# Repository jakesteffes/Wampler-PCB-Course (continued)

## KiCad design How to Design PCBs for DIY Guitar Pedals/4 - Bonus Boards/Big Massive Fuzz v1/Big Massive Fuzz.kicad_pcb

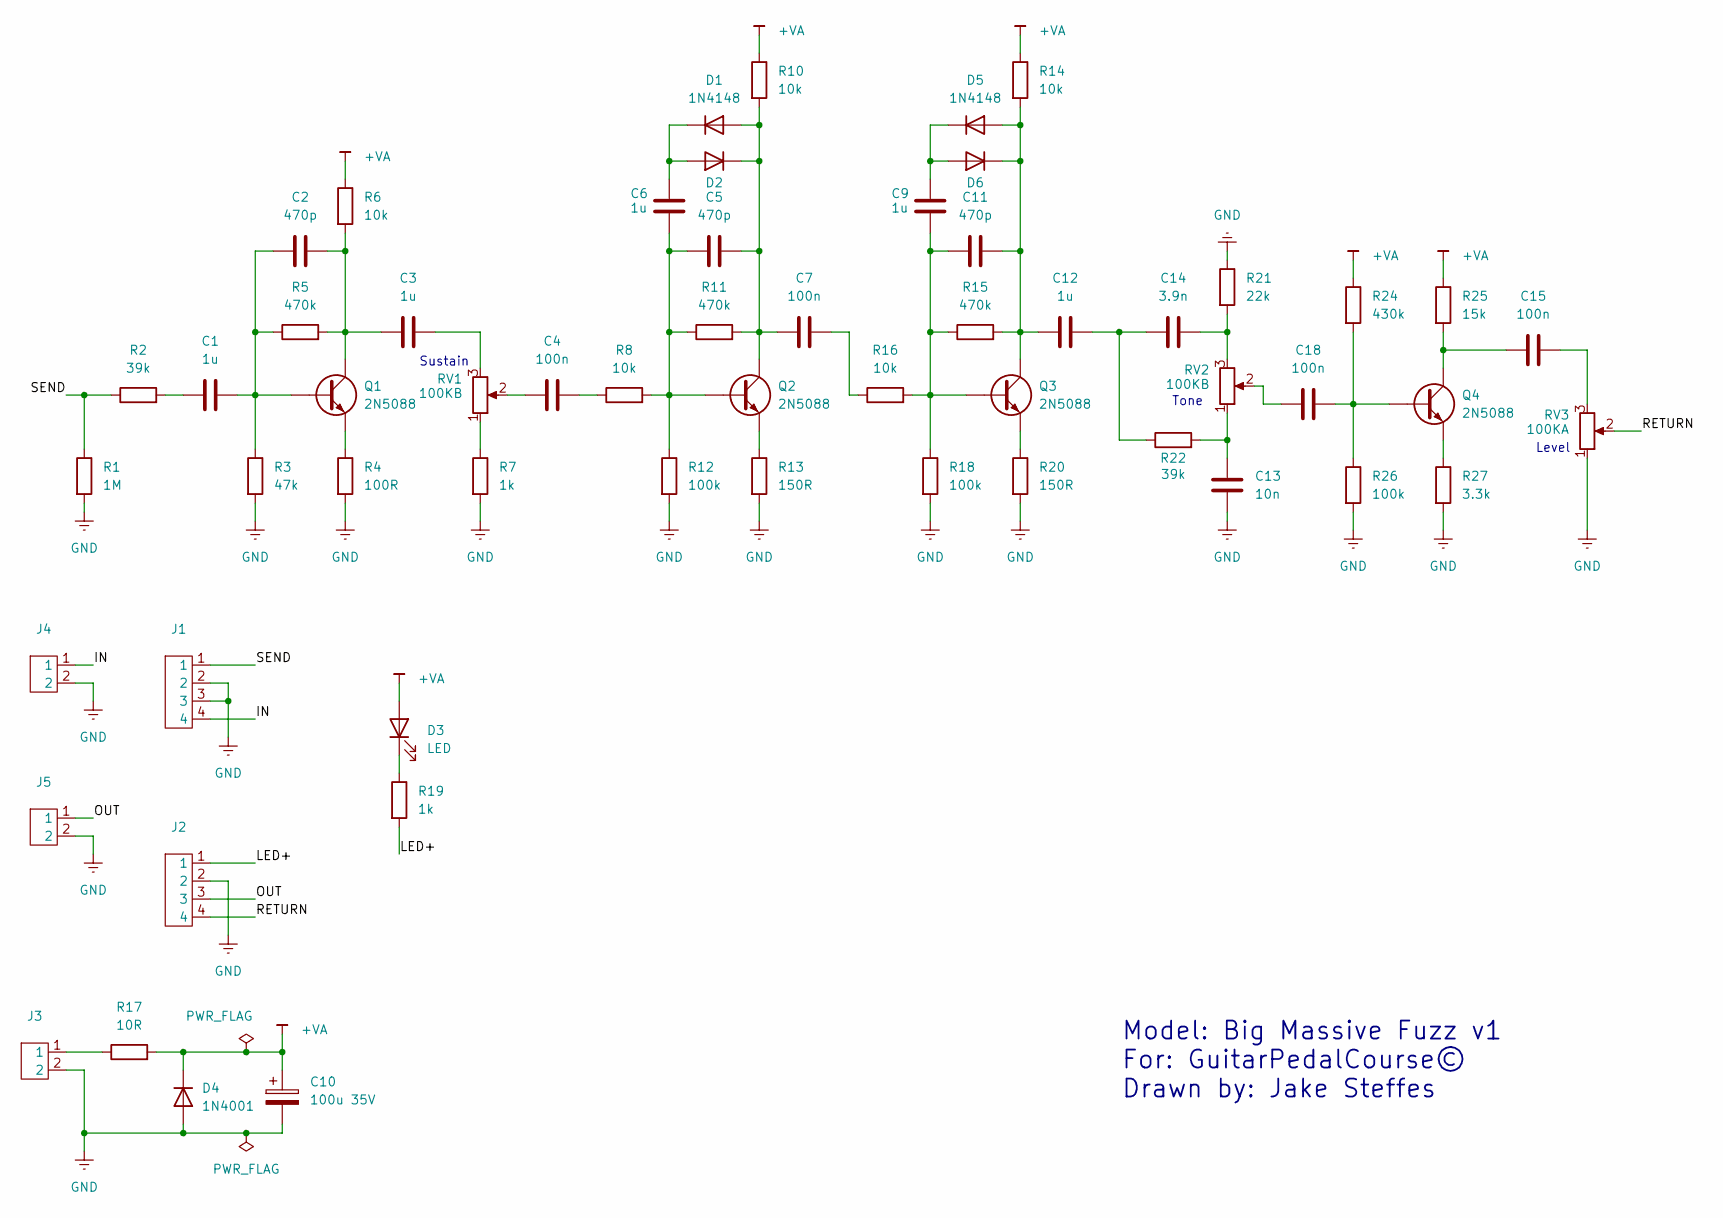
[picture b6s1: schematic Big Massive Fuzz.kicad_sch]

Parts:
C1, C3, C6, C9, C12: 1u; CAP_FILM_1UF
C2, C5, C11: 470p; CAP_MLCC_470PF
C4, C7, C15, C18: 100n; CAP_FILM_100NF
C10: 100u 35V; CAP_ELEC_100UF
C13: 10n; CAP_FILM_10NF
C14: 3.9n; CAP_MLCC_3.9NF
D1, D2, D5, D6: 1N4148; DIODE_1N4148
D3: LED; LED_5MM
D4: 1N4001; DIODE_1N4001
J1, J2: CONNECTOR_4
J3, J4, J5: CONNECTOR_2
Q1, Q2, Q3, Q4: 2N5088; BJT_2N5088
R1: 1M; RESISTOR_1_4W
R2, R22: 39k; RESISTOR_1_4W
R3: 47k; RESISTOR_1_4W
R4: 100R; RESISTOR_1_4W
R5, R11, R15: 470k; RESISTOR_1_4W
R6, R8, R10, R14, R16: 10k; RESISTOR_1_4W
R7, R19: 1k; RESISTOR_1_4W
R12, R18, R26: 100k; RESISTOR_1_4W
R13, R20: 150R; RESISTOR_1_4W
R17: 10R; RESISTOR_1_4W
R21: 22k; RESISTOR_1_4W
R24: 430k; RESISTOR_1_4W
R25: 15k; RESISTOR_1_4W
R27: 3.3k; RESISTOR_1_4W
RV1, RV2: 100KB; POT_16MM_RA
RV3: 100KA; POT_16MM_RA

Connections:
+VA: C10.1, D3.2 (A), D4.1 (K), R6.1, R10.1, R14.1, R17.2, R24.1, R25.1
/IN: J1.4, J4.1
/LED+: J2.1, R19.2
/OUT: J2.3, J5.1
/RETURN: J2.4, RV3.2
/SEND: J1.1, R1.1, R2.1
GND: C10.2, C13.1, D4.2 (A), J1.2, J1.3, J2.2, J3.2, J4.2, J5.2, R1.2, R3.2, R4.2, R7.2, R12.2, R13.2, R18.2, R20.2, R21.1, R26.2, R27.2, RV3.1
unnamed: C1.1, R2.2
unnamed: C1.2, C2.1, Q1.B, R3.1, R5.1
unnamed: C2.2, C3.1, Q1.C, R5.2, R6.2
unnamed: C3.2, RV1.3
unnamed: C4.1, RV1.2
unnamed: C4.2, R8.1
unnamed: C5.1, C6.1, Q2.B, R8.2, R11.1, R12.1
unnamed: C7.2, R16.1
unnamed: C9.1, C11.1, Q3.B, R15.1, R16.2, R18.1
unnamed: C12.2, C14.2, R22.1
unnamed: C13.2, R22.2, RV2.1
unnamed: C14.1, R21.2, RV2.3
unnamed: C15.1, Q4.C, R25.2
unnamed: C15.2, RV3.3
unnamed: C18.1, RV2.2
unnamed: C18.2, Q4.B, R24.2, R26.1
unnamed: C5.2, C7.1, D1.2 (A), D2.1 (K), Q2.C, R10.2, R11.2
unnamed: C6.2, D1.1 (K), D2.2 (A)
unnamed: D3.1 (K), R19.1
unnamed: C11.2, C12.1, D5.2 (A), D6.1 (K), Q3.C, R14.2, R15.2
unnamed: C9.2, D5.1 (K), D6.2 (A)
unnamed: J3.1, R17.1
unnamed: Q1.E, R4.1
unnamed: Q2.E, R13.1
unnamed: Q3.E, R20.1
unnamed: Q4.E, R27.1
unnamed: R7.1, RV1.1

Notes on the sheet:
Model: Big Massive Fuzz v1 For: GuitarPedalCourse© Drawn by: Jake Steffes
Level
Tone
Sustain

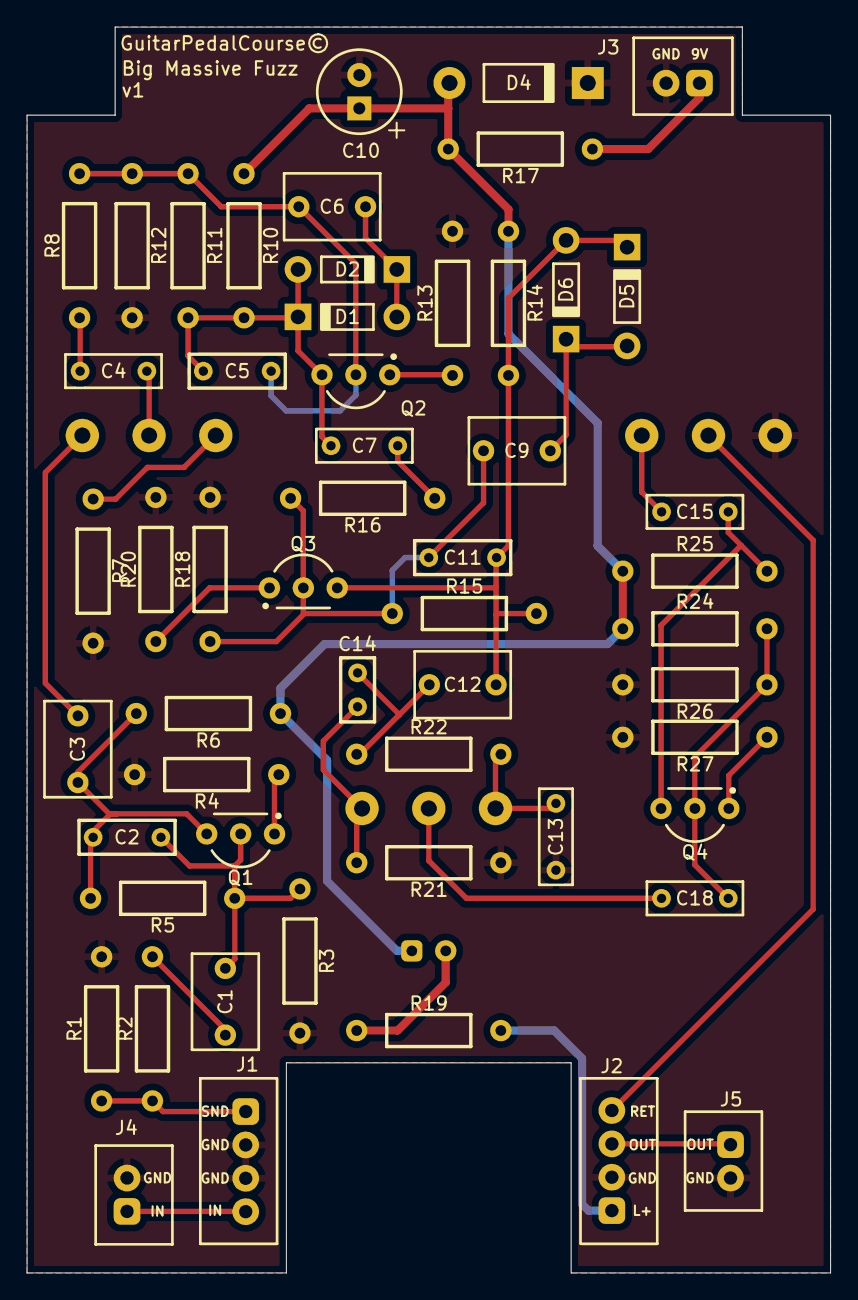
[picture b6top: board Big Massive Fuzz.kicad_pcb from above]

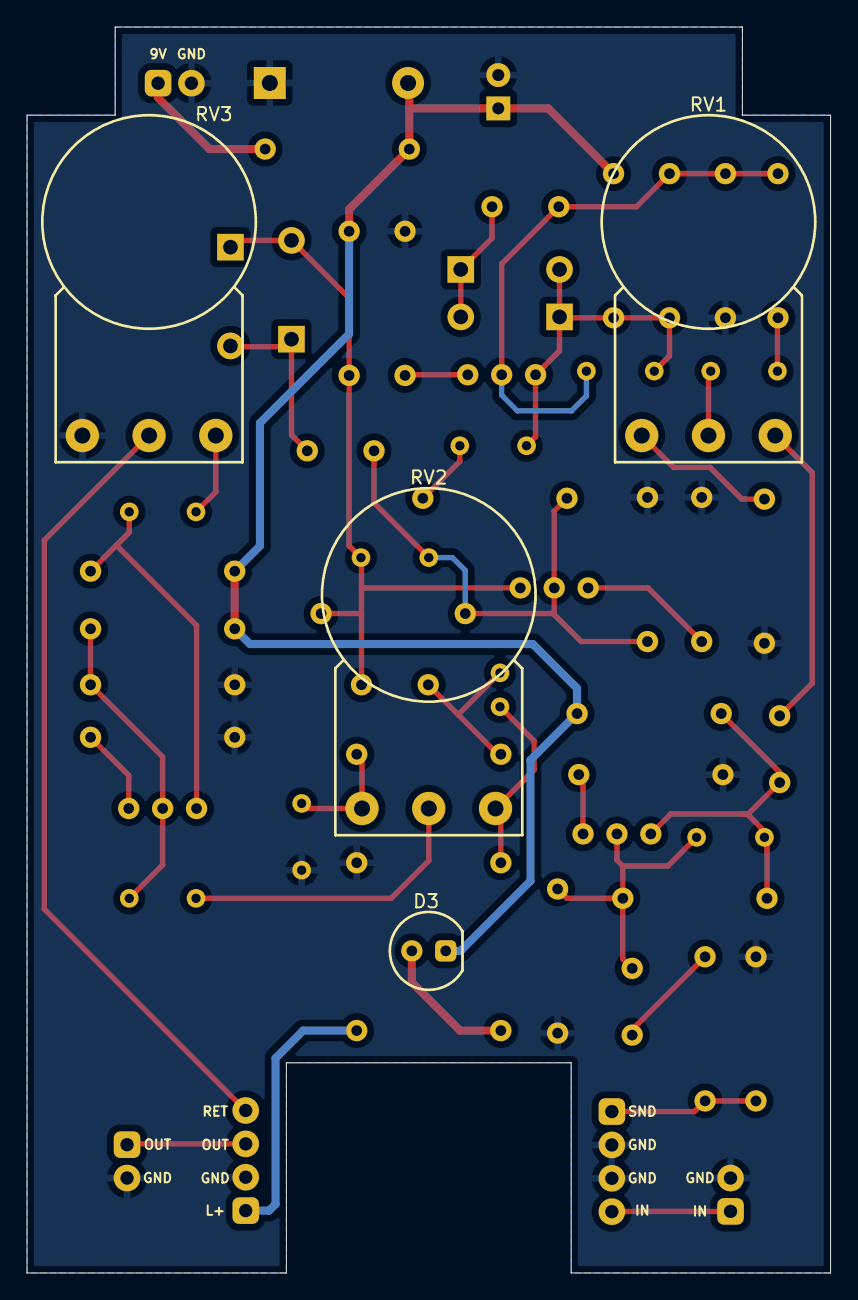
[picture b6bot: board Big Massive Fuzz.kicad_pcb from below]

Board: 2 copper layers, 60.2 x 93.3 mm, 58 parts (4 on the bottom side), 34 nets.

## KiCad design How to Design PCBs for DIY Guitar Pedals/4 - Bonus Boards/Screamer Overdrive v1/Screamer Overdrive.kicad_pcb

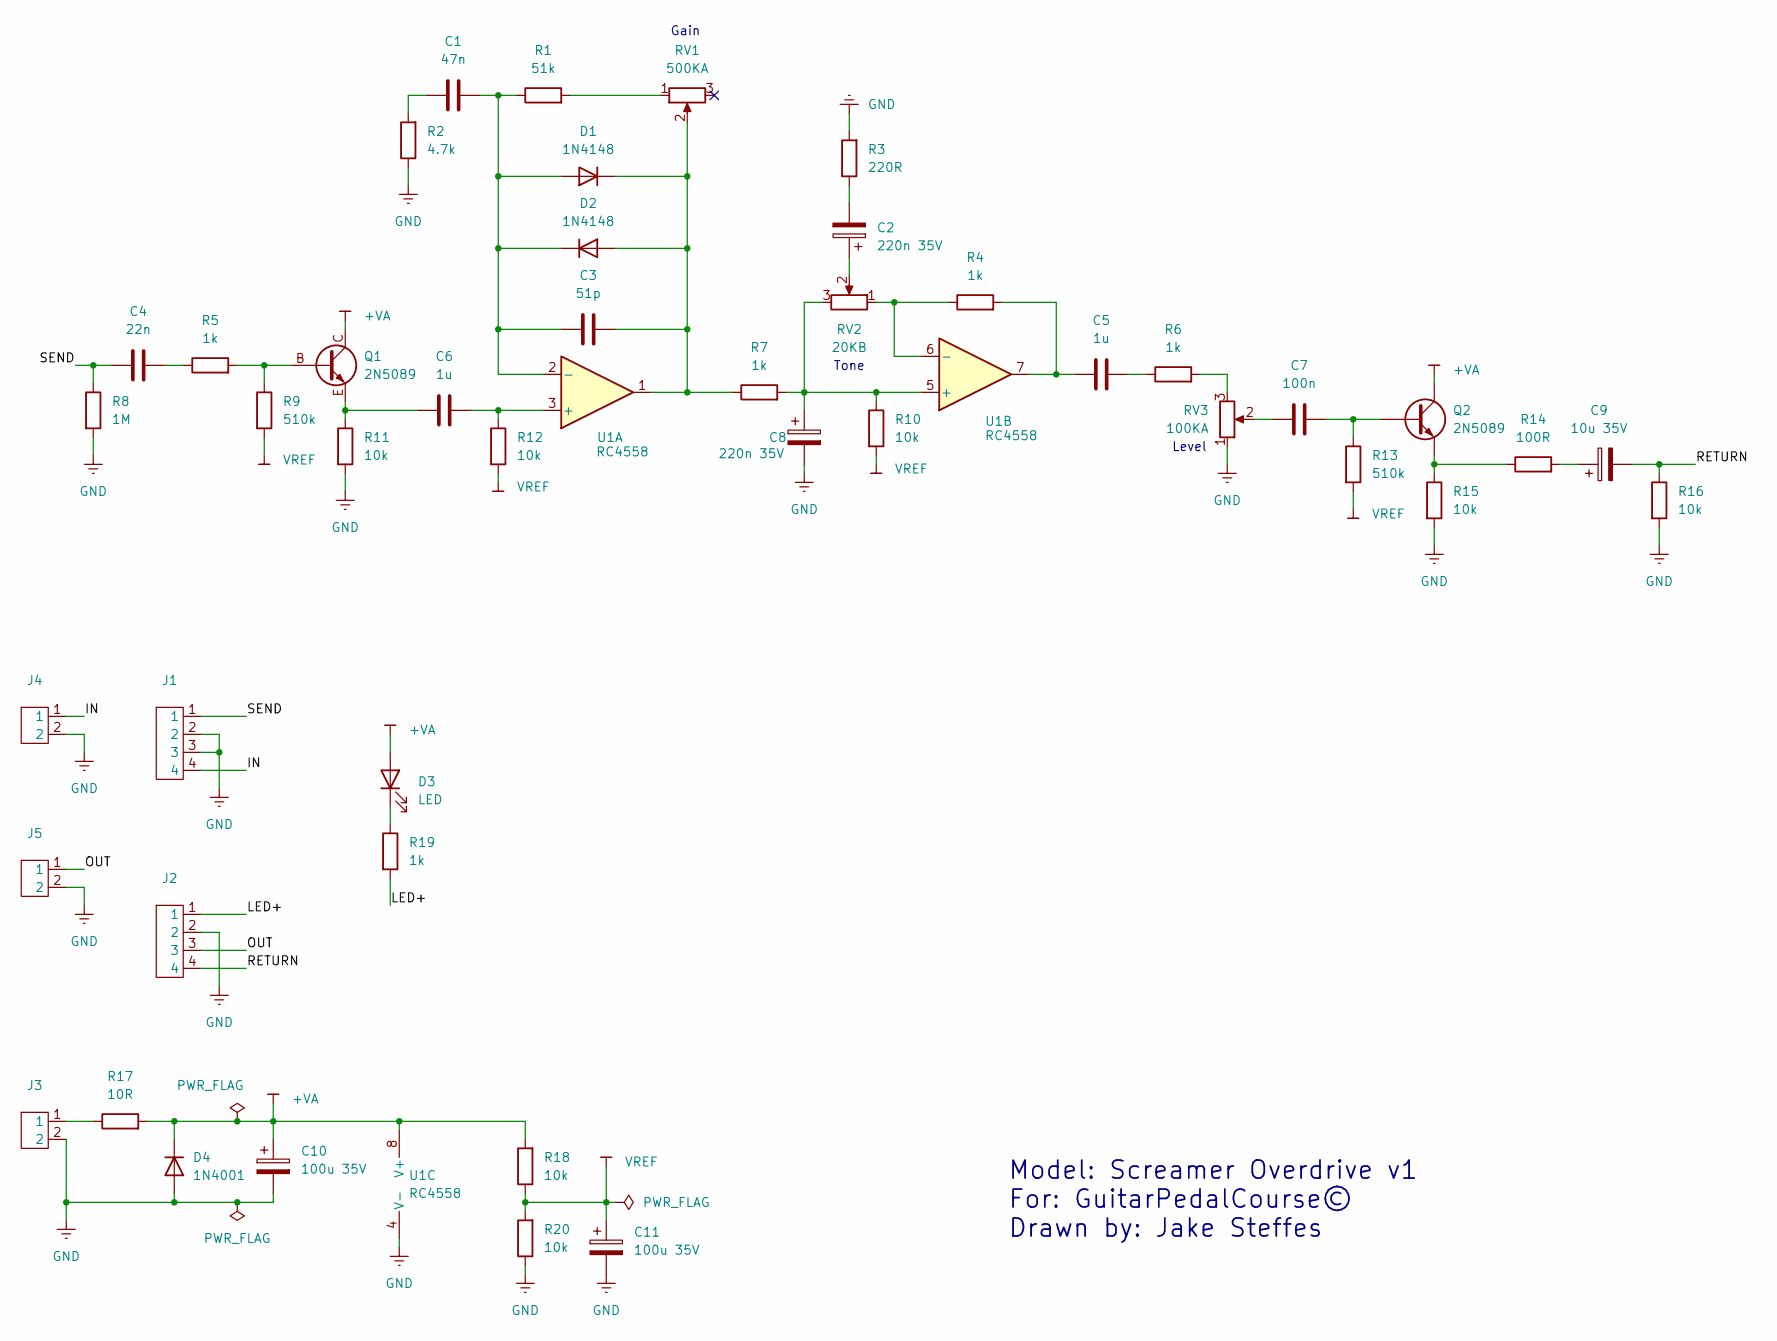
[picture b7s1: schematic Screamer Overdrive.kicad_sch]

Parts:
C1: 47n; CAP_FILM_47NF
C2, C8: 220n 35V; CAP_TANT_220NF
C3: 51p; CAP_MLCC_51PF
C4: 22n; CAP_FILM_22NF
C5, C6: 1u; CAP_FILM_1UF
C7: 100n; CAP_FILM_100NF
C9: 10u 35V; CAP_ELEC_10UF
C10, C11: 100u 35V; CAP_ELEC_100UF
D1, D2: 1N4148; DIODE_1N4148
D3: LED; LED_5MM
D4: 1N4001; DIODE_1N4001
J1, J2: CONNECTOR_4
J3, J4, J5: CONNECTOR_2
Q1, Q2: 2N5089; BJT_2N5089
R1: 51k; RESISTOR_1_4W
R2: 4.7k; RESISTOR_1_4W
R3: 220R; RESISTOR_1_4W
R4, R5, R6, R7, R19: 1k; RESISTOR_1_4W
R8: 1M; RESISTOR_1_4W
R9, R13: 510k; RESISTOR_1_4W
R10, R11, R12, R15, R16, R18, R20: 10k; RESISTOR_1_4W
R14: 100R; RESISTOR_1_4W
R17: 10R; RESISTOR_1_4W
RV1: 500KA; POT_16MM_RA
RV2: 20KB; POT_16MM_RA
RV3: 100KA; POT_16MM_RA
U1: RC4558; OP_AMP

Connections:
+VA: C10.1, D3.2 (A), D4.1 (K), Q1.C, Q2.C, R17.2, R18.2, U1.8 (V+)
/IN: J1.4, J4.1
/LED+: J2.1, R19.2
/OUT: J2.3, J5.1
/RETURN: C9.2, J2.4, R16.1
/SEND: C4.1, J1.1, R8.1
GND: C8.2, C10.2, C11.2, D4.2 (A), J1.2, J1.3, J2.2, J3.2, J4.2, J5.2, R2.1, R3.2, R8.2, R11.2, R15.2, R16.2, R20.1, RV3.1, U1.4 (V-)
unnamed: C1.1, R2.2
unnamed: C2.1, RV2.2
unnamed: C2.2, R3.1
unnamed: C4.2, R5.1
unnamed: C5.1, R4.2, U1.7
unnamed: C5.2, R6.1
unnamed: C6.1, Q1.E, R11.1
unnamed: C7.1, RV3.2
unnamed: C7.2, Q2.B, R13.1
unnamed: C9.1, R14.2
unnamed: C1.2, C3.1, D1.2 (A), D2.1 (K), R1.1, U1.2 (-)
unnamed: C3.2, D1.1 (K), D2.2 (A), R7.1, RV1.2, U1.1
unnamed: D3.1 (K), R19.1
unnamed: J3.1, R17.1
unnamed: Q1.B, R5.2, R9.1
unnamed: Q2.E, R14.1, R15.1
unnamed: R1.2, RV1.1
unnamed: R6.2, RV3.3
unnamed: C6.2, R12.1, U1.3 (+)
unnamed: C8.1, R7.2, R10.1, RV2.3, U1.5 (+)
unnamed: R4.1, RV2.1, U1.6 (-)
VREF: C11.1, R9.2, R10.2, R12.2, R13.2, R18.1, R20.2

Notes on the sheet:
Tone
Gain
Model: Screamer Overdrive v1 For: GuitarPedalCourse© Drawn by: Jake Steffes
Level

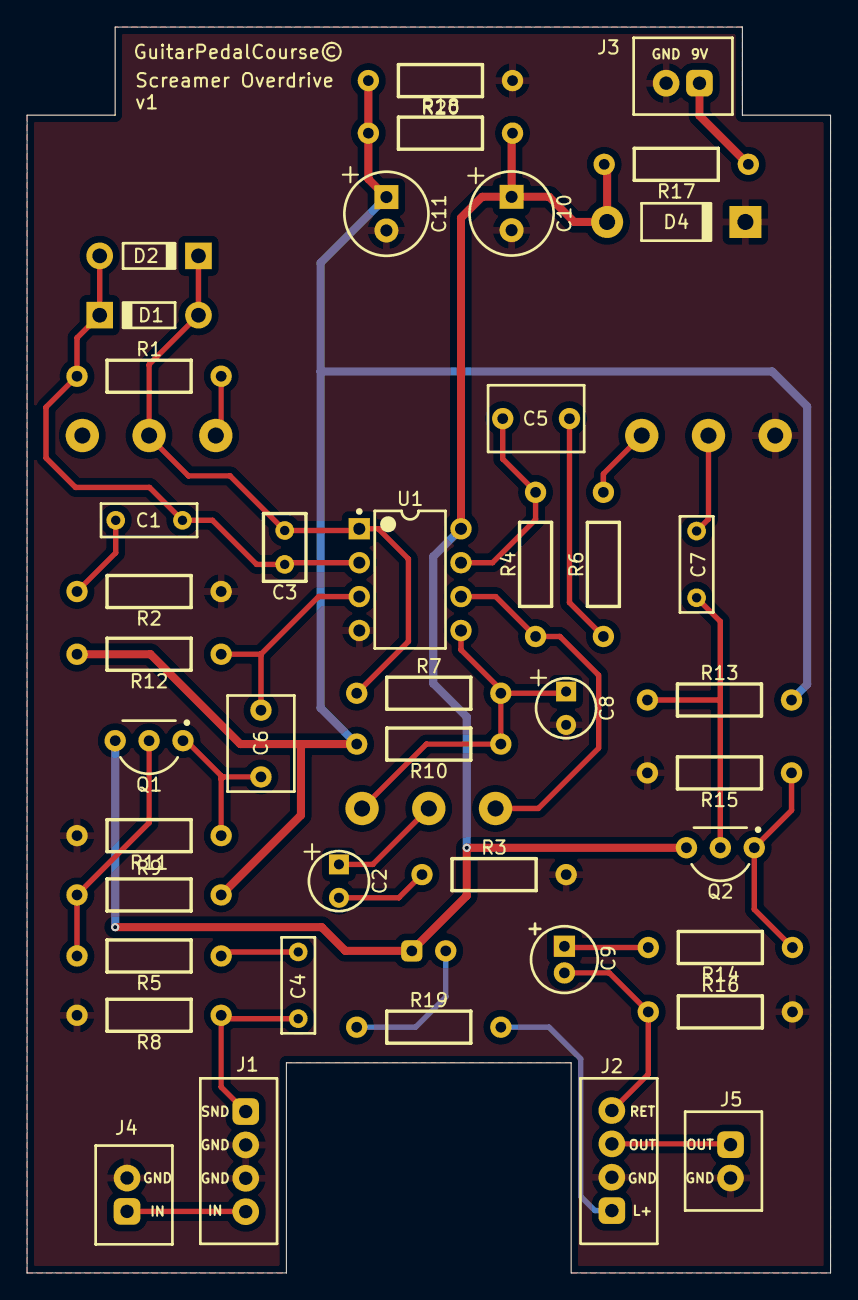
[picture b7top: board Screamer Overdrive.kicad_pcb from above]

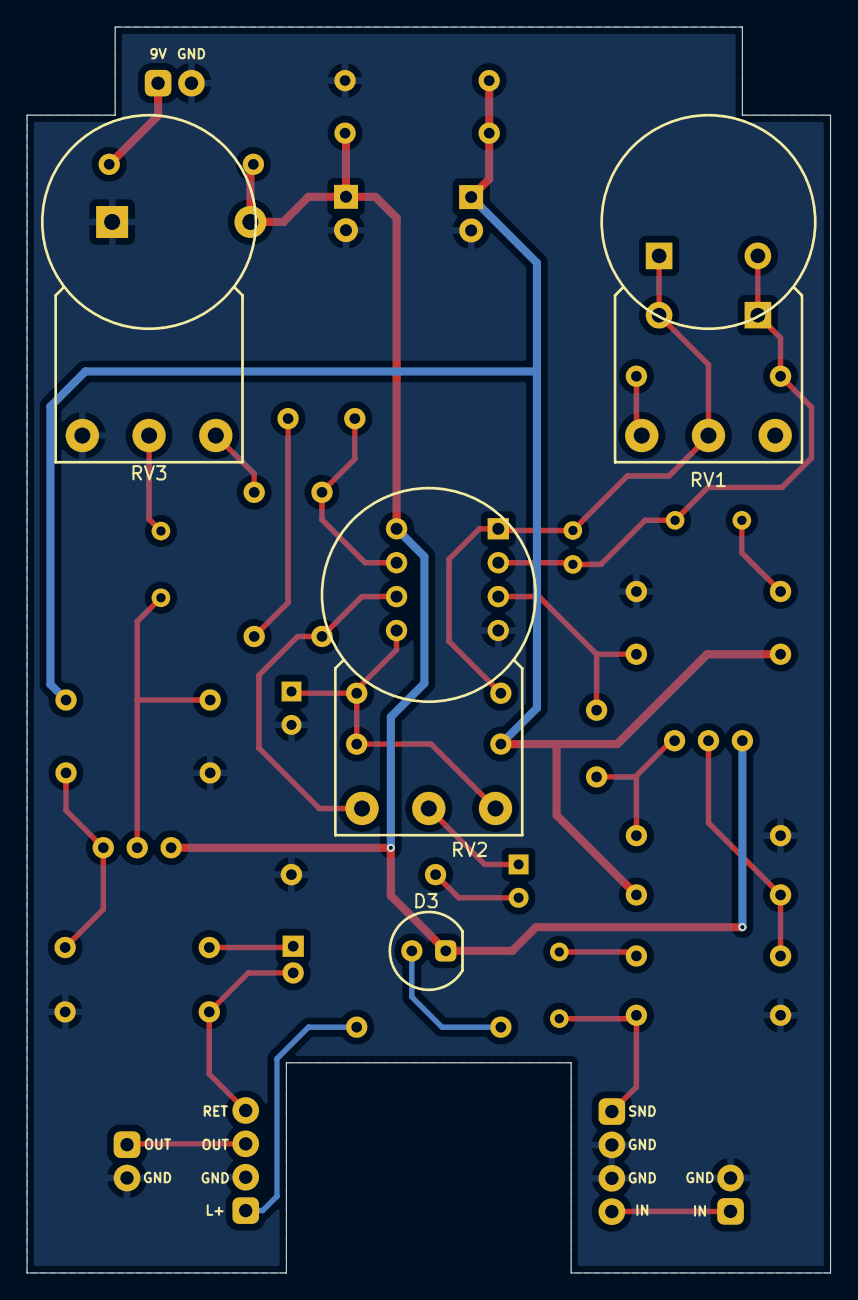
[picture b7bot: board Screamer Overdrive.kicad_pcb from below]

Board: 2 copper layers, 60.2 x 93.3 mm, 46 parts (4 on the bottom side), 29 nets.

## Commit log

2025-10-14 _init
2025-10-30 Libraries: fix CD4053B
